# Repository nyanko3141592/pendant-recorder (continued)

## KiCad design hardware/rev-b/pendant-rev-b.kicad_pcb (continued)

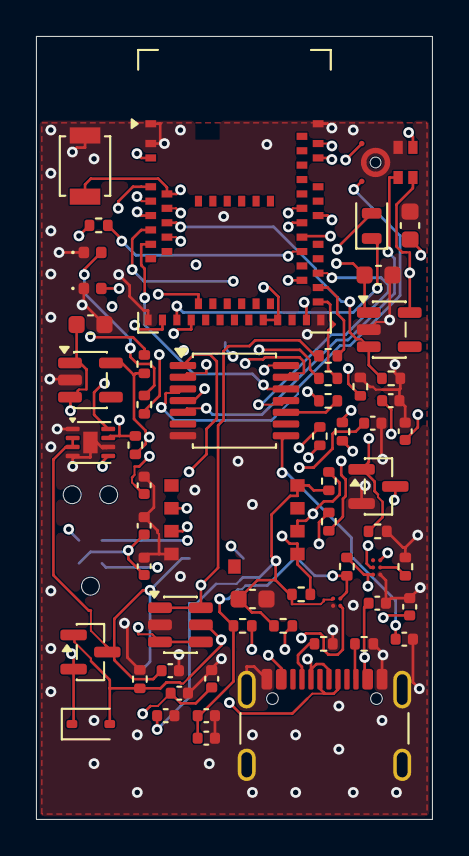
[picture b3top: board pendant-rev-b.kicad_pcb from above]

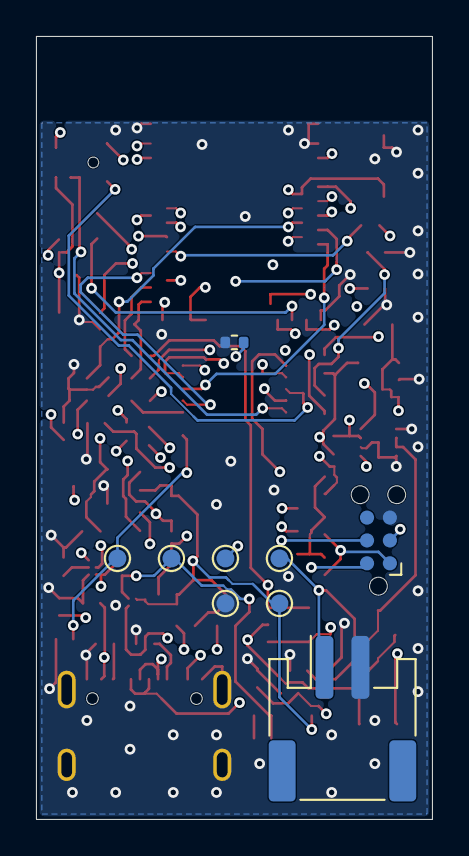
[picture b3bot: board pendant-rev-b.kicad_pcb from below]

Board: 4 copper layers, 22.0 x 43.5 mm, 68 parts (9 on the bottom side), 46 nets.

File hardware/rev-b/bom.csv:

Reference,Part/value,Footprint,Design note
U1,MDBT50Q-1MV2,RF_Module:Raytac_MDBT50Q,"Raytac Ver L p40: normal voltage, VDD=VDDH=3V, DCCH NC; Reg1 DCDC inside. RF clearance required."
C1,100n,Capacitor_SMD:C_0402_1005Metric,
C4,10u,Capacitor_SMD:C_0603_1608Metric,10u VDD/VDDH decoupling per Raytac p40; effective capacitance review pending.
C9,100n,Capacitor_SMD:C_0402_1005Metric,
R2,10k,Resistor_SMD:R_0402_1005Metric,
Y1,32.768kHz CL=7pF TBD,Crystal:Crystal_SMD_2012-2Pin_2.0x1.2mm,
C11,10p tentative,Capacitor_SMD:C_0402_1005Metric,
C12,10p tentative,Capacitor_SMD:C_0402_1005Metric,
J3,TC2030 SWD target pads,Connector:Tag-Connect_TC2030-IDC-NL_2x03_P1.27mm_Vertical,"VTref,SWDIO,nRESET,SWCLK,GND,NC; use nRF-compatible completed J-Link probe/cable, not STM32 STLINK assumption."
SW1,B3U-1000P (candidate),Button_Switch_SMD:SW_SPST_B3U-1000P,
R4,100k,Resistor_SMD:R_0402_1005Metric,
R5,3.3k,Resistor_SMD:R_0402_1005Metric,
D1,red LED,LED_SMD:LED_0402_1005Metric,
J1,USB4105-GF-A (candidate),Connector_USB:USB_C_Receptacle_GCT_USB4105-xx-A_16P_TopMnt_Horizontal,Exact footprint and shield pad numbering pending connector selection
R6,5.1k 1%,Resistor_SMD:R_0402_1005Metric,
R7,5.1k 1%,Resistor_SMD:R_0402_1005Metric,
R8,27R 1%,Resistor_SMD:R_0402_1005Metric,Raytac reference p40 USB series resistor; signal integrity validation pending.
R9,27R 1%,Resistor_SMD:R_0402_1005Metric,Raytac reference p40 USB series resistor; signal integrity validation pending.
U2,USBLC6-2SC6,Package_TO_SOT_SMD:SOT-23-6,Verify footprint; short path to connector ground
C13,2.2u 10V,Capacitor_SMD:C_0402_1005Metric,
U3,BQ25101YFPR,Pendant:BQ25101_YFP6,"BQ25101, 21.81mA nominal with 6.19k 1%; TS NTC must contact cell. Temperature/timeout validation pending."
R10,6.19k 1%,Resistor_SMD:R_0402_1005Metric,BQ25101: nominal 21.81mA; KISET max145 / (6190*0.99)=23.66mA < DTP max55mA. Standard pack charging approximately22mA.
R11,100k,Resistor_SMD:R_0402_1005Metric,
C14,2.2u,Capacitor_SMD:C_0402_1005Metric,
J2,S2B-PH-SM4-TB(LF)(SN) / DTP401525 110mAh,Connector_JST:JST_PH_S2B-PH-SM4-TB_1x02-1MP_P2.00mm_Horizontal,"Two-pin PH pack connection. Confirm delivered polarity. TH1 is PCB-mounted thermal contact, no third battery wire."
TH1,NCP15XH103F03RC 10k NTC,Resistor_SMD:R_0402_1005Metric,PCB-mounted NTC thermally coupled to pack through insulation. Position/contact/thermal response require validation; no hand-soldered harness.
Q2,2N7002 (charge inhibit),Package_TO_SOT_SMD:SOT-23,High disables charging by pulling TS low; USB suspend policy required
R12,100k,Resistor_SMD:R_0402_1005Metric,
D2,BAT54WS (candidate; leakage/forward drop review pending),Diode_SMD:D_SOD-323,USB path; characterize leakage and input inrush
Q1,DMP2035U (candidate; power path review pending),Package_TO_SOT_SMD:SOT-23,"S=SYS, D=BAT intentionally; body diode BAT -> SYS; exact MPN/pinout pending"
R16,100k,Resistor_SMD:R_0402_1005Metric,
C15,4.7u,Capacitor_SMD:C_0603_1608Metric,
U4,TPS7A0230PDBVR,Package_TO_SOT_SMD:SOT-23-5,DBV / SOT23-5 prototype; miniaturization later
U6,TPS7A0218PDBVR,Package_TO_SOT_SMD:SOT-23-5,DBV / SOT23-5 prototype; miniaturization later
C16,1u,Capacitor_SMD:C_0402_1005Metric,
C18,1u,Capacitor_SMD:C_0402_1005Metric,
C19,1u,Capacitor_SMD:C_0402_1005Metric,
C20,10u 10V,Capacitor_SMD:C_0603_1608Metric,Raytac reference p40 VBUS capacitor; USB total input capacitance/inrush validation REQUIRED before release.
R17,100k,Resistor_SMD:R_0402_1005Metric,
U7,MAX17048G+T10,Package_DFN_QFN:TDFN-8-1EP_2x2mm_P0.5mm_EP0.8x1.2mm,EP pad number 9 is footprint convention; verify footprint
C21,100n,Capacitor_SMD:C_0402_1005Metric,
R18,4.7k,Resistor_SMD:R_0402_1005Metric,
R19,4.7k,Resistor_SMD:R_0402_1005Metric,
R20,100k,Resistor_SMD:R_0402_1005Metric,
U8,T5838,Pendant:T5838_LGA7_BottomPort,BOTTOM port; 1.62..1.98V only; SELECT low = right channel
U9,TXS0104EPWR,Package_SO:TSSOP-14_4.4x5mm_P0.65mm,TI SCES651K table 5-3; JLC C44955 exact TSSOP-14 catalog match. Avoid 0.4mm DSBGA central-pad escape requirement.
R21,22R tentative,Resistor_SMD:R_0402_1005Metric,
C22,100n,Capacitor_SMD:C_0402_1005Metric,
C23,100n,Capacitor_SMD:C_0402_1005Metric,
C24,100n,Capacitor_SMD:C_0402_1005Metric,
U10,TPS22916CYFPR,Pendant:TPS22916_YFP4,Omi SD switch; power-off sequence must tristate ALL SD signals
R22,100k,Resistor_SMD:R_0402_1005Metric,
C25,1u,Capacitor_SMD:C_0402_1005Metric,
U11,CSNP32GCR01-BOW,Pendant:CSNP32GCR01_LGA8,SPI mode per manufacturer p2; unused DAT1/DAT2 reserved; verify power-up and interrupted-write behavior.
R23,22R tentative,Resistor_SMD:R_0402_1005Metric,
R24,47k,Resistor_SMD:R_0402_1005Metric,
R25,47k,Resistor_SMD:R_0402_1005Metric,
R28,47k,Resistor_SMD:R_0402_1005Metric,
C26,100n,Capacitor_SMD:C_0402_1005Metric,
C27,22u effective TBD,Capacitor_SMD:C_0603_1608Metric,
TP1,TestPoint,TestPoint:TestPoint_Pad_D1.0mm,
TP2,TestPoint,TestPoint:TestPoint_Pad_D1.0mm,
TP3,TestPoint,TestPoint:TestPoint_Pad_D1.0mm,
TP4,TestPoint,TestPoint:TestPoint_Pad_D1.0mm,
TP5,TestPoint,TestPoint:TestPoint_Pad_D1.0mm,
TP6,TestPoint,TestPoint:TestPoint_Pad_D1.0mm,
R32,6.8k tentative,Resistor_SMD:R_0402_1005Metric,"LED current target 0.1-0.2mA; verify LED Vf, daylight readability and GPIO limits"
D6,amber LED 0402 TBD,LED_SMD:LED_0402_1005Metric,Battery level by blink count; shared charging/error indication; exact LED MPN pending.

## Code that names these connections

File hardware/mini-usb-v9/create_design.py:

from pathlib import Path
import json,copy,shutil
P=Path(__file__).parent; S=P.parent/'compact-100-v5'
d=json.loads((S/'design.json').read_text());d['revision']='mini-usb-v9'
remove={'U6','U9','C18','C19','C23','C24','R17','TP4','D1','R5','Q1','D2','R16','Q2'}
d['parts']=[p for p in d['parts'] if p['ref'] not in remove]; ps={p['ref']:p for p in d['parts']}
def pin(n,name,net,t='passive'):return dict(number=str(n),name=name,net=net,type=t)
for p in ps['U1']['pins']:
 if p['net'] in ['MIC_WAKE','MIC_THSEL','MIC_EN','REC_LED']:p['net']=None
ps['U8'].update(value='IM69D130V01XTSA1',footprint='Sensor_Audio:Infineon_PG-LLGA-5-1',pins=[pin(1,'DATA','PDM_DATA','output'),pin(2,'VDD','V3V3','power_in'),pin(3,'CLOCK','PDM_CLK','input'),pin(4,'SELECT','GND','input'),pin(5,'GND','GND','power_in')],note='Direct 3.3V PDM, bottom port; no AAD. 0.768MHz/decimation48 candidate for 16kHz; acoustic validation required.')
ps['C22']['pins'][0]['net']='V3V3'
ps['U3'].update(value='BQ25185DLHR',footprint='Package_DFN_QFN:Texas_DLH0010A_WSON-10-1EP_2.2x2mm_P0.4mm_EP0.9x1.5mm',pins=[pin(1,'SYS','SYS','power_out'),pin(2,'BAT','BAT','passive'),pin(3,'STAT2',None,'open_collector'),pin(4,'CE_N','CHG_INHIBIT_GATE','input'),pin(5,'GND','GND','power_in'),pin(6,'TS_MR','CHARGER_TS','input'),pin(7,'ILIM_VSET','ILIM_VSET','input'),pin(8,'ISET','ISET','input'),pin(9,'STAT1','CHG_N','open_collector'),pin(10,'IN','VBUS','power_in'),pin(11,'EP','GND','passive')],note='Integrated power path; 4.2V/100mA input via24k; 20mA charge via15k. Independent U12/Q4 battery NTC guard retained; internal TS biased10k is NOT battery temperature sensing.')
ps['R10']['value']='15k 1%';ps['R11']['value']='20k 1%';ps['C15']['value']='10u 10V effective >=1u';ps['C15']['note']='SYS cap per TI; DC-bias capacitance must be qualified.'
ps['J2']['value']='0781710003 / 100mAh protected NTC pack TBD'
ps['J2']['note']='15x17x6 pack envelope retained; vendor NTC/finished connector and harness unqualified.'
ps['D6']['note']='Single status/battery indicator; firmware blinks on demand, normally dark.'
ps['U11'].update(value='CSNP4GCR01-DPW',footprint='Pendant:CSNP4GCR01_DPW_LGA8',note='512MiB nominal, SPI. Same pin assignment as previous; package drawing checked. Out of stock at LCSC; capacity must be read from CSD. One-day ADPCM capacity only, no auto-delete.')
for r,value,net,base in [('R42','24k 1%','ILIM_VSET','R10'),('C30','10n tentative','ISET','C28')]:
 p=copy.deepcopy(ps[base]);p.update(ref=r,value=value,note='BQ25185 reference application; verify tolerance and low-current startup RC.');p['pins'][0]['net']=net;d['parts'].append(p)
# Open-drain comparator outputs share a gate clamp: either fault overrides MCU permission.
ps['U12']['value']='TLV7042DDFR'
for p in ps['U12']['pins']:
 if p['number'] in ['1','7']:p.update(net='CHG_GUARD_GATE',type='open_collector')
ps['U12']['note']='Open-drain outputs wired together. Either temperature fault pulls Q4 gate low; no firmware override. 10k/B3370 pack assumption remains unqualified.'
ps['Q4']['pins'][0]['net']='CHG_GUARD_GATE';ps['Q4']['pins'][2]['net']='CHG_INHIBIT_GATE'
ps['R36']['pins'][0]['net']='CHG_GUARD_GATE'
p=copy.deepcopy(ps['R10']);p.update(ref='R43',value='10k 1%',note='MCU permission series resistor; limits current into comparator fault clamp.')
p['pins'][0]['net']='CHG_ALLOW';p['pins'][1]['net']='CHG_GUARD_GATE';d['parts'].append(p)
d['parts']=[p for p in d['parts'] if p['ref'] not in ['Q5','Q6']]
(P/'design.json').write_text(json.dumps(d,indent=2)+'\n')
for name in ['Pendant.pretty','PendantD1.pretty']:shutil.copytree(S/name,P/name,dirs_exist_ok=True)
s=(S/'Pendant.pretty/CSNP32GCR01_LGA8.kicad_mod').read_text().replace('CSNP32GCR01_LGA8','CSNP4GCR01_DPW_LGA8').replace('-3.1','-3.0').replace('4.0 3.1','4.0 3.0').replace('-3.35','-3.25').replace('4.25 3.35','4.25 3.25').replace('(at 0 2.6)','(at 0 2.5)')
(P/'Pendant.pretty/CSNP4GCR01_DPW_LGA8.kicad_mod').write_text(s)
s=(S/'generate_schematic.py').read_text().replace("'compact-100-v5'","'mini-usb-v9'").replace("['GND','VDDA','VBUS','SYS']","['GND','VDDA','VBUS']")
(P/'generate_schematic.py').write_text(s)
s=(S/'fp-lib-table').read_text().replace('\n)\n','\n(lib (name "Sensor_Audio") (type "KiCad") (uri "${KICAD10_FOOTPRINT_DIR}/Sensor_Audio.pretty") (options "") (descr ""))\n)\n');(P/'fp-lib-table').write_text(s)
shutil.copy(S/'pendant-compact-100-v5.kicad_pro',P/'pendant-mini-usb-v9.kicad_pro')
# Remove failed downloads generated during source research; not documents.
for name in ['mp34dt06j.pdf','im69d130.pdf']:
 f=P/'reference'/name
 if f.exists() and not f.read_bytes().startswith(b'%PDF'):f.unlink()
print(len(d['parts']),'footprints',len(d['parts'])-6,'populated')
